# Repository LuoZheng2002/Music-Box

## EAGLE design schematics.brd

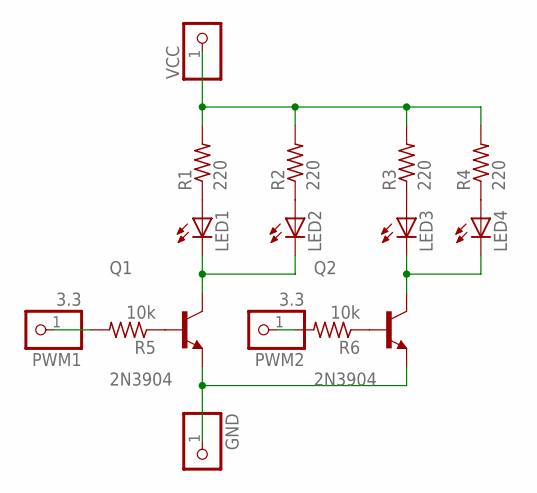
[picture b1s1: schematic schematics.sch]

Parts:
GND: PINHD-1X1; 1X01
LED1, LED2, LED3, LED4: LED5MM
PWM1, PWM2: 3.3; 1X01
Q1, Q2: 2N3904; TO92127P495H495-3
R1, R2, R3, R4: 220; 0309/10
R5, R6: 10k; 0309/10
VCC: PINHD-1X1; 1X01

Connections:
unnamed: Q2.2 (B), R6.1
unnamed: LED1.A, R1.1
unnamed: LED1.K (C), LED2.K (C), Q1.3 (C)
unnamed: LED2.A, R2.1
unnamed: Q1.2 (B), R5.1
unnamed: LED3.A, R3.1
unnamed: LED4.A, R4.1
unnamed: LED3.K (C), LED4.K (C), Q2.3 (C)
unnamed: PWM1.1, R5.2
unnamed: PWM2.1, R6.2
unnamed: R1.2, R2.2, R3.2, R4.2, VCC.1
unnamed: GND.1, Q1.1 (E), Q2.1 (E)

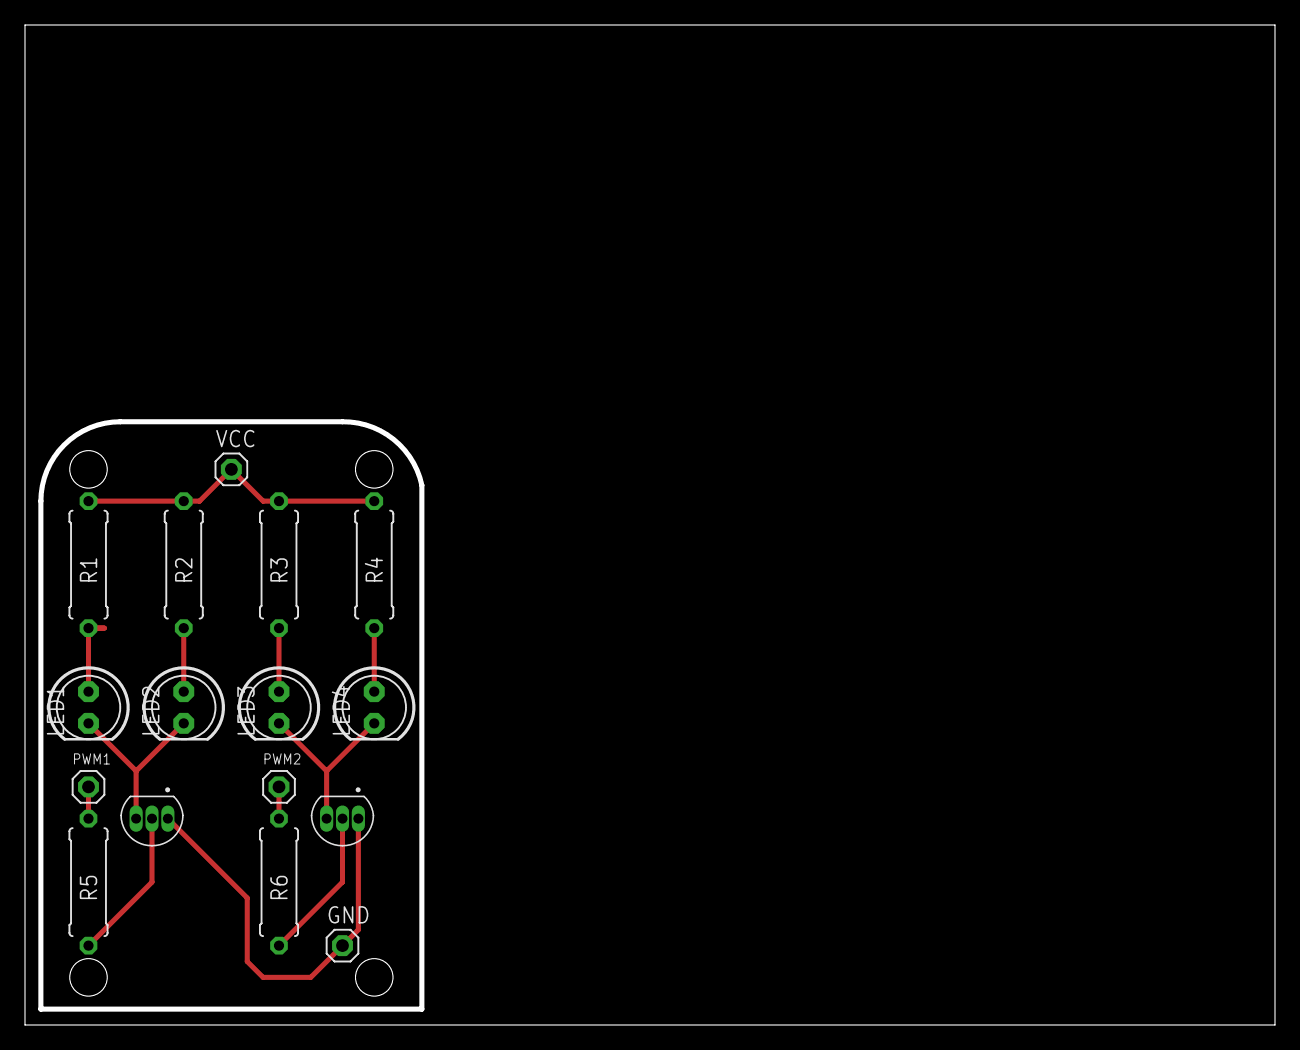
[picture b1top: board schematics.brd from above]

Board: 2 copper layers, 99.6 x 79.6 mm, 16 parts (0 on the bottom side), 12 nets.

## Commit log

2023-12-21 checkpoint
2023-12-21 checkpoint2
